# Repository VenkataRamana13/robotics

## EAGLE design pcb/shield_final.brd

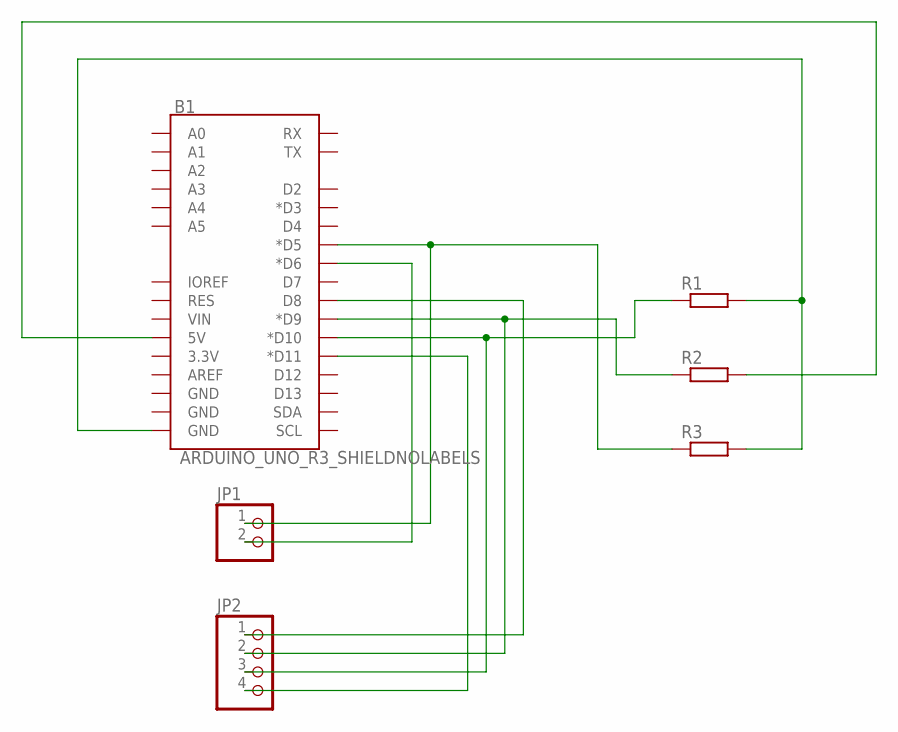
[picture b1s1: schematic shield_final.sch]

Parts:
B1: ARDUINO_UNO_R3_SHIELDNOLABELS; UNO_R3_SHIELD_NOLABELS
JP1: PINHD-1X2; 1X02
JP2: PINHD-1X4; 1X04
R1, R2, R3: R-EU_0207/10; 0207/10

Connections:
unnamed: B1.D8, JP2.1
unnamed: B1.D9 (*D9), JP2.2, R2.1
unnamed: B1.D10 (*D10), JP2.3, R1.1
unnamed: B1.D11 (*D11), JP2.4
unnamed: B1.D5 (*D5), JP1.1, R3.1
unnamed: B1.D6 (*D6), JP1.2
unnamed: B1.GND@0 (GND), R1.2, R3.2
unnamed: B1.5V, R2.2

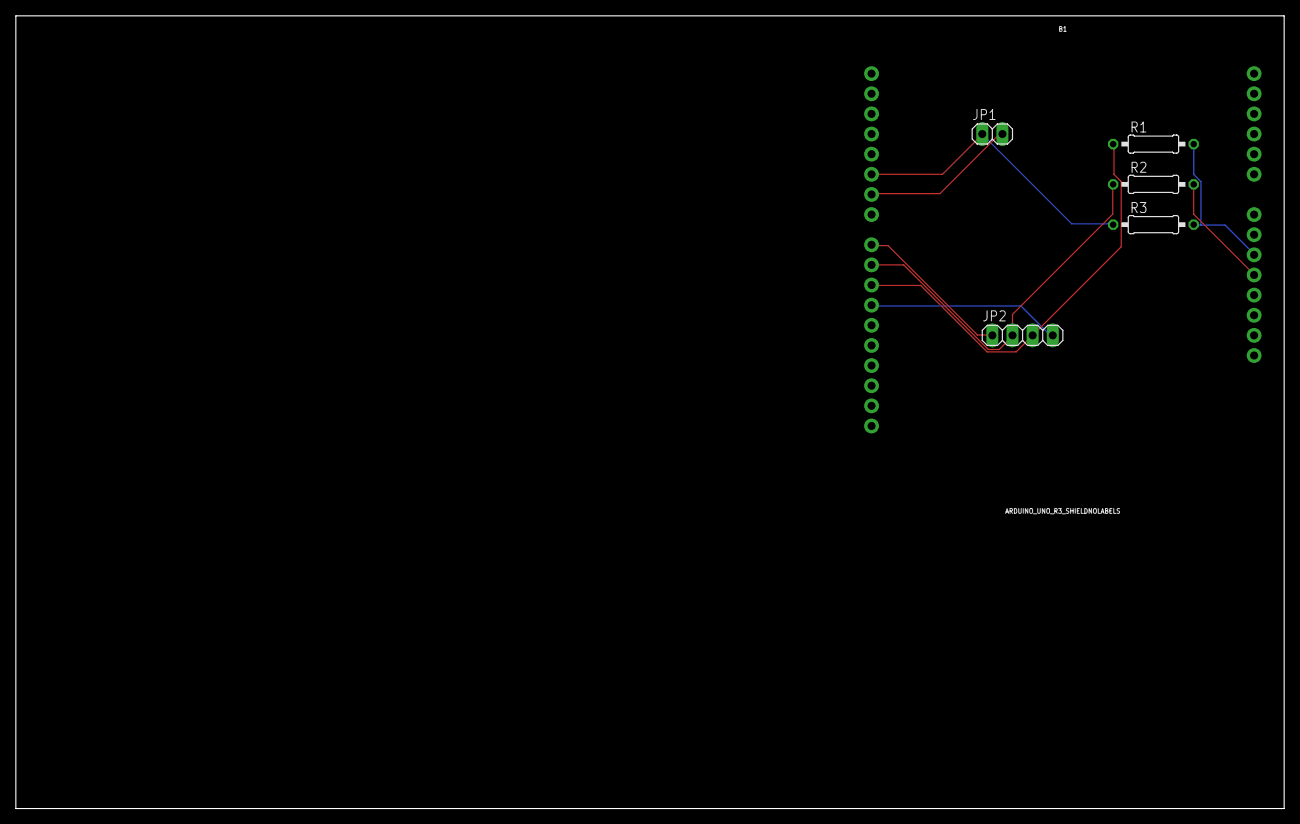
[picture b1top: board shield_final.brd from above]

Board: 2 copper layers, 160.0 x 100.0 mm, 6 parts (0 on the bottom side), 8 nets.

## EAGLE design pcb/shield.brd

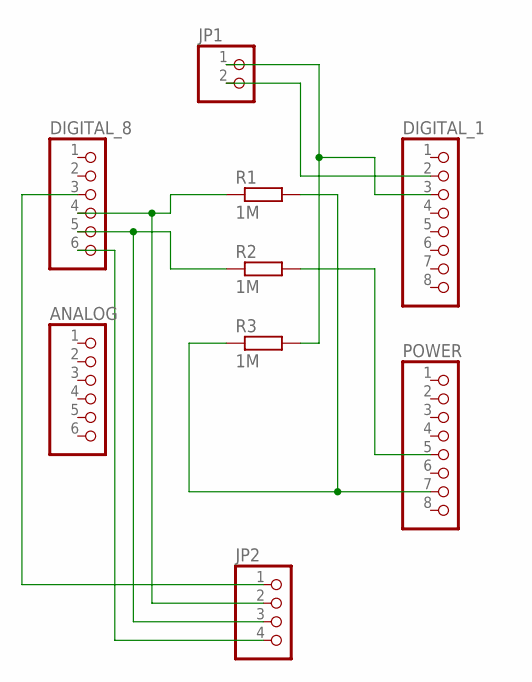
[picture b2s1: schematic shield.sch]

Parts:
ANALOG: PINHD-1X6; 1X06
DIGITAL_1: PINHD-1X8; 1X08
DIGITAL_8: PINHD-1X6; 1X06
JP1: PINHD-1X2; 1X02
JP2: PINHD-1X4; 1X04
POWER: PINHD-1X8; 1X08
R1, R2, R3: 1M; 0207/10

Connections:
unnamed: POWER.7, R1.2, R3.1
unnamed: DIGITAL_8.4, JP2.2, R1.1
unnamed: DIGITAL_8.5, JP2.3, R2.1
unnamed: POWER.5, R2.2
unnamed: DIGITAL_1.3, JP1.1, R3.2
unnamed: DIGITAL_8.6, JP2.4
unnamed: DIGITAL_8.3, JP2.1
unnamed: DIGITAL_1.2, JP1.2

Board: 2 copper layers, 9 parts (0 on the bottom side), 8 nets, no tracks yet.

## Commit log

2022-03-16 notes.txt
2022-03-16 hello_blink.cpp
2022-06-10 Create t

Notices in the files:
parts and their libraries:
SparkFun-Boards: Licensing: Creative Commons ShareAlike 4.0 International - https://creativecommons.org/licenses/by-sa/4.0
